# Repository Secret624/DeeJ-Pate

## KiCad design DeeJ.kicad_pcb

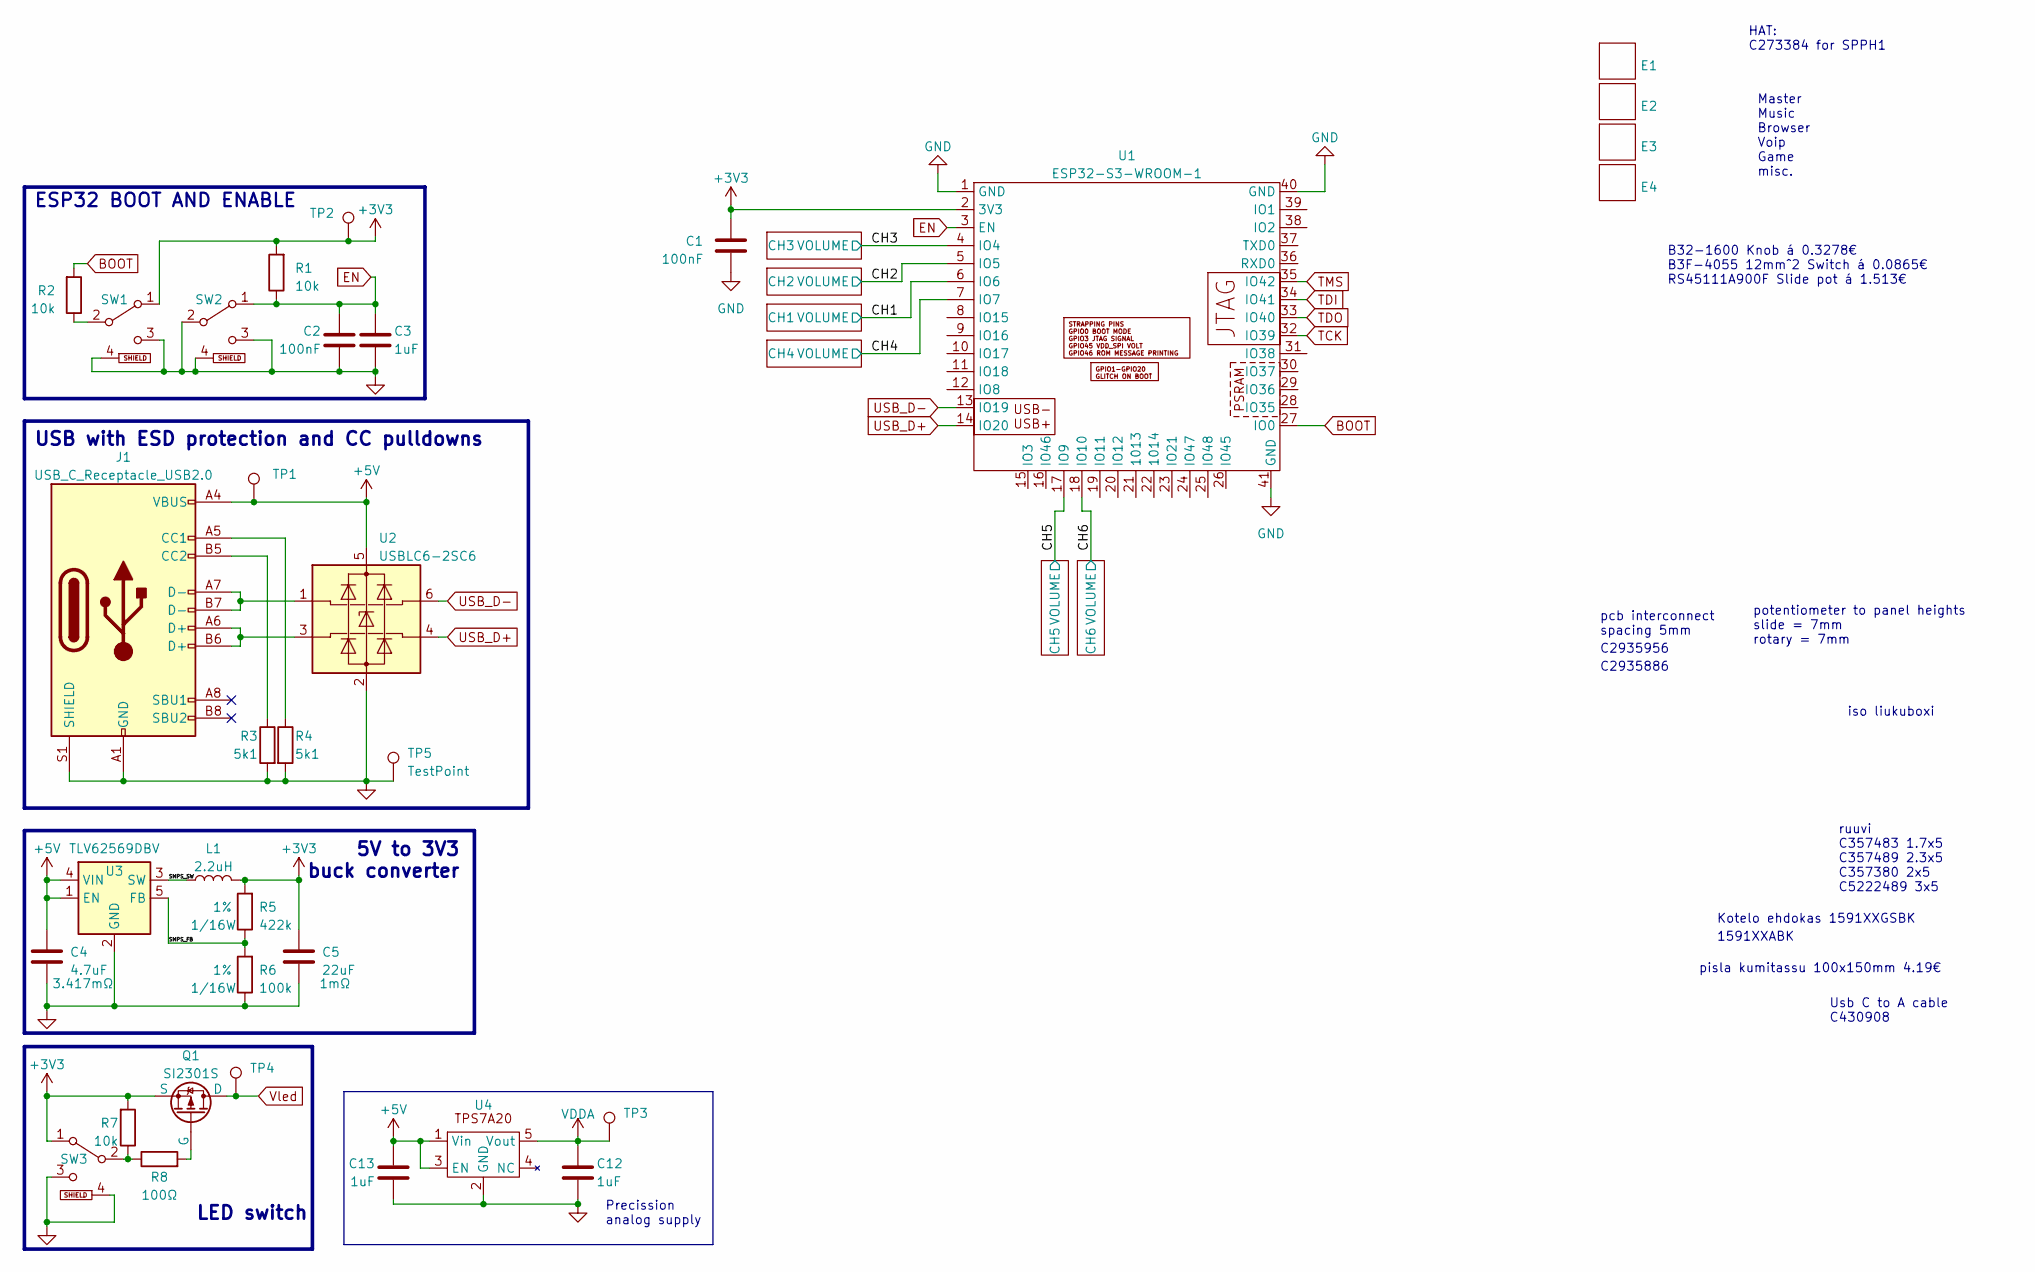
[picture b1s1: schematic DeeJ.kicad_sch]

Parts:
C1, C2: 100nF; C_0805_2012Metric_Pad1.18x1.45mm_HandSolder
C3, C12, C13: 1uF; C_0805_2012Metric_Pad1.18x1.45mm_HandSolder
C4: 4.7uF; C_1206_3216Metric_Pad1.33x1.80mm_HandSolder; LCSC# C527983
C5: 22uF; C_0805_2012Metric_Pad1.18x1.45mm_HandSolder; LCSC# C92814
E1, E2, E3, E4: FIX-SF-664
J1: USB_C_Receptacle_USB2.0; USB_C_Receptacle_HRO_TYPE-C-31-M-12; LCSC# C165948
L1: 2.2uH; L_TDK_VLS6045EX_VLS6045AF_handsolder; Mouser# 810-VLS6045EX-2R2N
Q1: SI2301S; SOT-23
R1, R2: 10k; R_0805_2012Metric_Pad1.20x1.40mm_HandSolder
R3, R4: 5k1; R_0603_1608Metric_Pad0.98x0.95mm_HandSolder
R5: 422k; R_0603_1608Metric_Pad0.98x0.95mm_HandSolder; Tolerance 1%
R6: 100k; R_0603_1608Metric_Pad0.98x0.95mm_HandSolder; Tolerance 1%
R7: 10k; R_0603_1608Metric_Pad0.98x0.95mm_HandSolder
R8: 100Ω; R_0603_1608Metric_Pad0.98x0.95mm_HandSolder
SW1, SW2, SW3: SW_SPDT; SK-3296S-01
TP1, TP2, TP3, TP4: TestPoint; TestPoint_Pad_D2.0mm
TP5: TestPoint; TestPoint_Pad_4.0x4.0mm
U1: ESP32-S3-WROOM-1
U2: USBLC6-2SC6; SOT-23-6; LCSC# C2687116
U3: TLV62569DBV; SOT-23-5
U4: SOT-23-5; LCSC# C2877858

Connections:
+3V3: C1.1, C5.1, L1.2, Q1.3 (S), R1.2, R5.2, R7.2, SW1.1 (A), SW3.1 (A), TP2.1, U1.2 (3V3)
+5V: C4.1, C13.1, J1.A4 (VBUS), J1.A9 (VBUS), J1.B4 (VBUS), J1.B9 (VBUS), TP1.1, U2.5 (VBUS), U3.1 (EN), U3.4 (VIN), U4.1 (Vin), U4.3 (EN)
/CH1: U1.6 (IO6); also elsewhere on the board
/CH2: U1.5 (IO5); also elsewhere on the board
/CH3: U1.4 (IO4); also elsewhere on the board
/CH4: U1.7 (IO7); also elsewhere on the board
/CH5: U1.17 (IO9); also elsewhere on the board
/CH6: U1.18 (IO10); also elsewhere on the board
/SMPS_FB: R5.1, R6.2, U3.5 (FB)
/SMPS_SW: L1.1, U3.3 (SW)
BOOT: R2.2, U1.27 (IO0)
EN: C2.1, C3.1, R1.1, SW2.1 (A), U1.3 (EN)
GND: C1.2, C2.2, C3.2, C4.2, C5.2, C12.2, C13.2, J1.A1 (GND), J1.A12 (GND), J1.B1 (GND), J1.B12 (GND), J1.S1 (SHIELD), R3.2, R4.2, R6.1, SW1.3 (C), SW1.4 (Shield), SW2.2 (B), SW2.3 (C), SW2.4 (Shield), SW3.3 (C), SW3.4 (Shield), TP5.1, U1.1 (GND), U1.40 (GND), U1.41 (GND), U2.2 (GND), U3.2 (GND), U4.2 (GND); also elsewhere on the board
unnamed: J1.A5 (CC1), R4.1
unnamed: J1.B5 (CC2), R3.1
unnamed: J1.A6 (D+), J1.B6 (D+), U2.3 (I/O1)
unnamed: J1.A7 (D-), J1.B7 (D-), U2.1 (I/O1)
unnamed: Q1.2 (G), R8.2
unnamed: R2.1, SW1.2 (B)
unnamed: R7.1, R8.1, SW3.2 (B)
TCK: U1.32 (IO39)
TDI: U1.34 (IO41)
TDO: U1.33 (IO40)
TMS: U1.35 (IO42)
USB_D+: U1.14 (IO20), U2.4 (I/O2)
USB_D-: U1.13 (IO19), U2.6 (I/O2)
VDDA: C12.1, TP3.1, U4.5 (Vout); also elsewhere on the board
Vled: Q1.1 (D), TP4.1; also elsewhere on the board

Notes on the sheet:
Precission analog supply
Kotelo ehdokas 1591XXGSBK
C2935886
pcb interconnect spacing 5mm
ruuvi C357483 1.7x5 C357489 2.3x5 C357380 2x5 C5222489 3x5
LED switch
B32-1600 Knob á 0.3278€ B3F-4055 12mm^2 Switch á 0.0865€ RS45111A900F Slide pot á 1.513€
potentiometer to panel heights slide = 7mm rotary = 7mm
pisla kumitassu 100x150mm 4.19€
ESP32 BOOT AND ENABLE
C2935956
1591XXABK
HAT: C273384 for SPPH1
iso liukuboxi
5V to 3V3 buck converter
USB with ESD protection and CC pulldowns
Master Music Browser Voip Game misc.
Usb C to A cable C430908

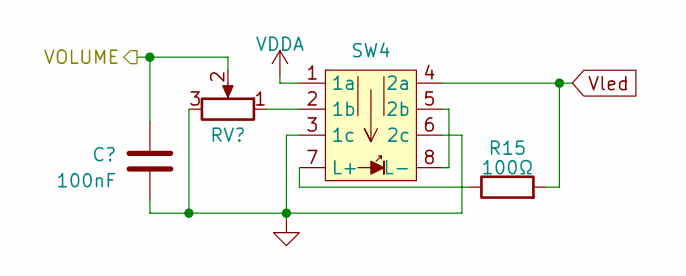
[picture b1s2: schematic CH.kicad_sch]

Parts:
C6: 100nF; C_0603_1608Metric_Pad1.08x0.95mm_HandSolder
R15: 100Ω; R_0603_1608Metric_Pad0.98x0.95mm_HandSolder
RV1: R_Potentiometer; RS45111A900F
SW4: K6-6133D

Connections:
/CH1: C6.1, RV1.2; also elsewhere on the board
GND: C6.2, RV1.3, SW4.3 (1c), SW4.6 (2c); also elsewhere on the board
unnamed: RV1.1, SW4.2 (1b)
unnamed: SW4.5 (2b), SW4.8 (L-)
unnamed: R15.1, SW4.7 (L+)
VDDA: SW4.1 (1a); also elsewhere on the board
Vled: R15.2, SW4.4 (2a); also elsewhere on the board

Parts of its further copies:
C7, C8, C9, C10, C11: 100nF; C_0603_1608Metric_Pad1.08x0.95mm_HandSolder
R16, R17, R18, R19, R20: 100Ω; R_0603_1608Metric_Pad0.98x0.95mm_HandSolder
RV2, RV3, RV4, RV5, RV6: R_Potentiometer; RS45111A900F
SW5, SW6, SW7, SW8, SW9: K6-6133D

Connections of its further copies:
/CH2: C7.1, RV2.2; also elsewhere on the board
/CH3: C8.1, RV3.2; also elsewhere on the board
/CH4: C9.1, RV4.2; also elsewhere on the board
/CH5: C10.1, RV5.2; also elsewhere on the board
/CH6: C11.1, RV6.2; also elsewhere on the board
GND: C7.2, C8.2, C9.2, C10.2, C11.2, RV2.3, RV3.3, RV4.3, RV5.3, RV6.3, SW5.3 (1c), SW5.6 (2c), SW6.3 (1c), SW6.6 (2c), SW7.3 (1c), SW7.6 (2c), SW8.3 (1c), SW8.6 (2c), SW9.3 (1c), SW9.6 (2c); also elsewhere on the board
unnamed: RV2.1, SW5.2 (1b)
unnamed: SW5.5 (2b), SW5.8 (L-)
unnamed: R16.1, SW5.7 (L+)
unnamed: RV3.1, SW6.2 (1b)
unnamed: SW6.5 (2b), SW6.8 (L-)
unnamed: R17.1, SW6.7 (L+)
unnamed: RV4.1, SW7.2 (1b)
unnamed: SW7.5 (2b), SW7.8 (L-)
unnamed: R18.1, SW7.7 (L+)
unnamed: RV5.1, SW8.2 (1b)
unnamed: SW8.5 (2b), SW8.8 (L-)
unnamed: R19.1, SW8.7 (L+)
unnamed: RV6.1, SW9.2 (1b)
unnamed: SW9.5 (2b), SW9.8 (L-)
unnamed: R20.1, SW9.7 (L+)
VDDA: SW5.1 (1a), SW6.1 (1a), SW7.1 (1a), SW8.1 (1a), SW9.1 (1a); also elsewhere on the board
Vled: R16.2, R17.2, R18.2, R19.2, R20.2, SW5.4 (2a), SW6.4 (2a), SW7.4 (2a), SW8.4 (2a), SW9.4 (2a); also elsewhere on the board

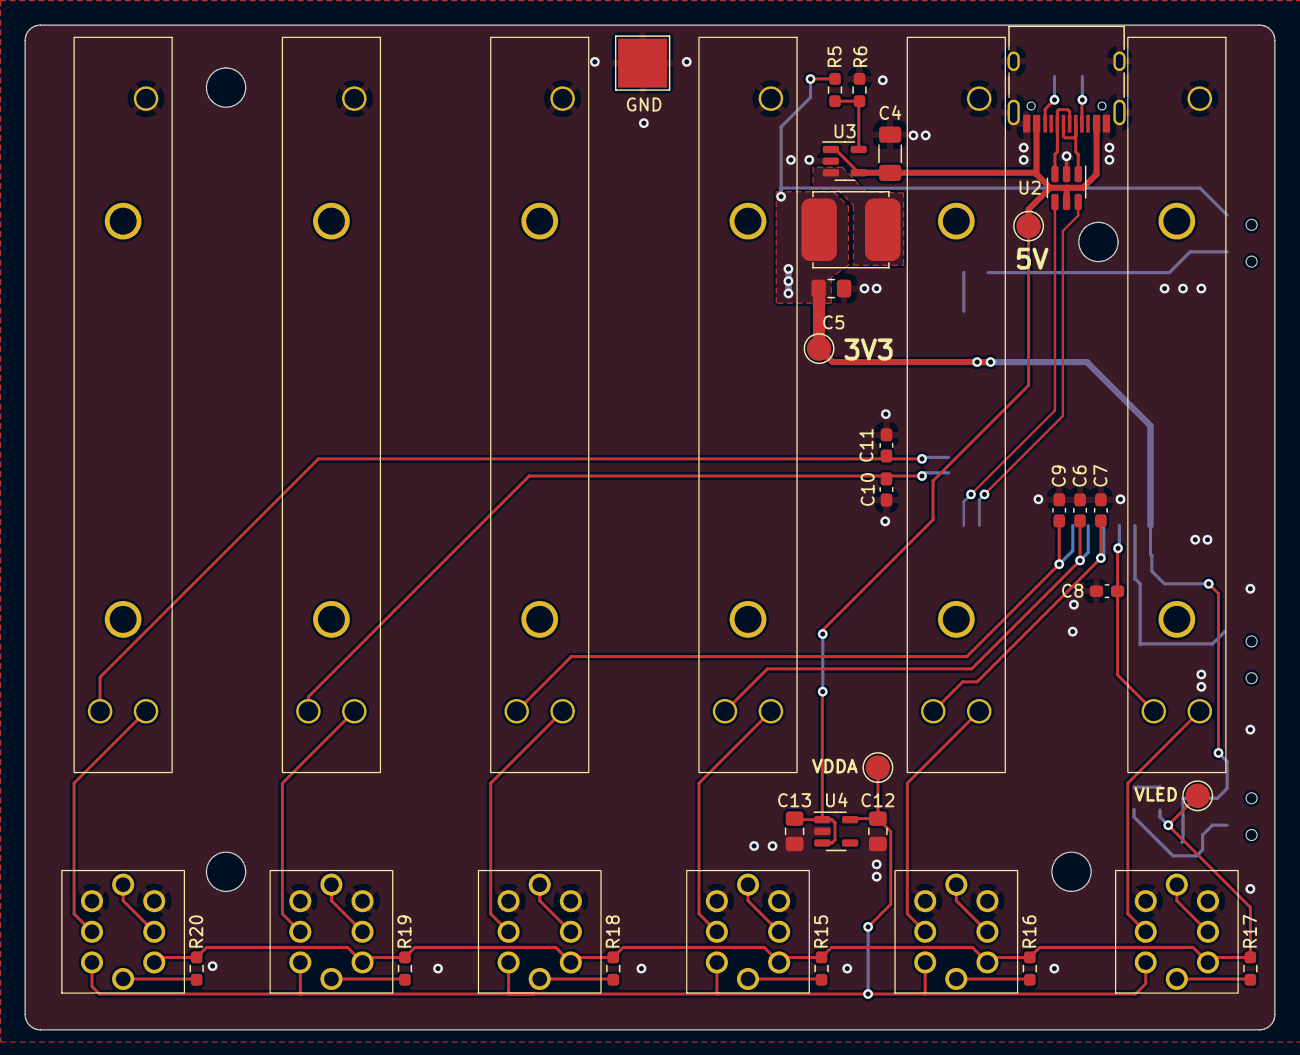
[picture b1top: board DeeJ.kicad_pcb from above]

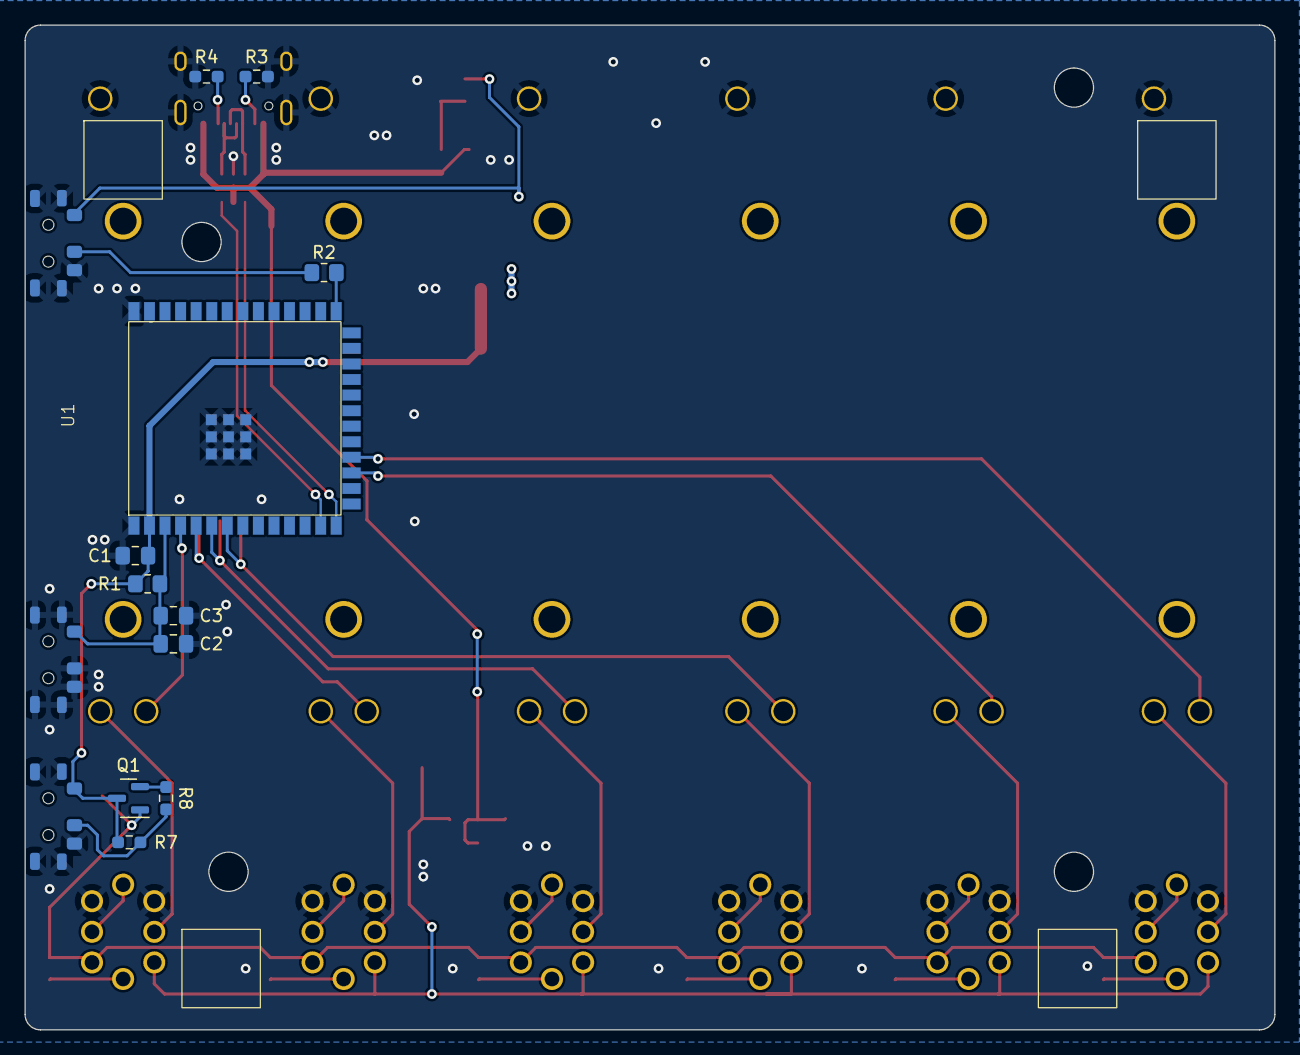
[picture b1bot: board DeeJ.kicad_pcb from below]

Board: 2 copper layers, 102.0 x 82.0 mm, 58 parts (18 on the bottom side), 42 nets.

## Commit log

2024-03-28 Added 3D models Move 3Dmallit to Kicad\7.0\share\kicad\3dmodels
2024-03-28 Small fixes
2024-04-14 Added arduino sketch
2024-04-21 webdeej added
2024-05-09 final design 1.0
2024-05-30 Smallest fixes
